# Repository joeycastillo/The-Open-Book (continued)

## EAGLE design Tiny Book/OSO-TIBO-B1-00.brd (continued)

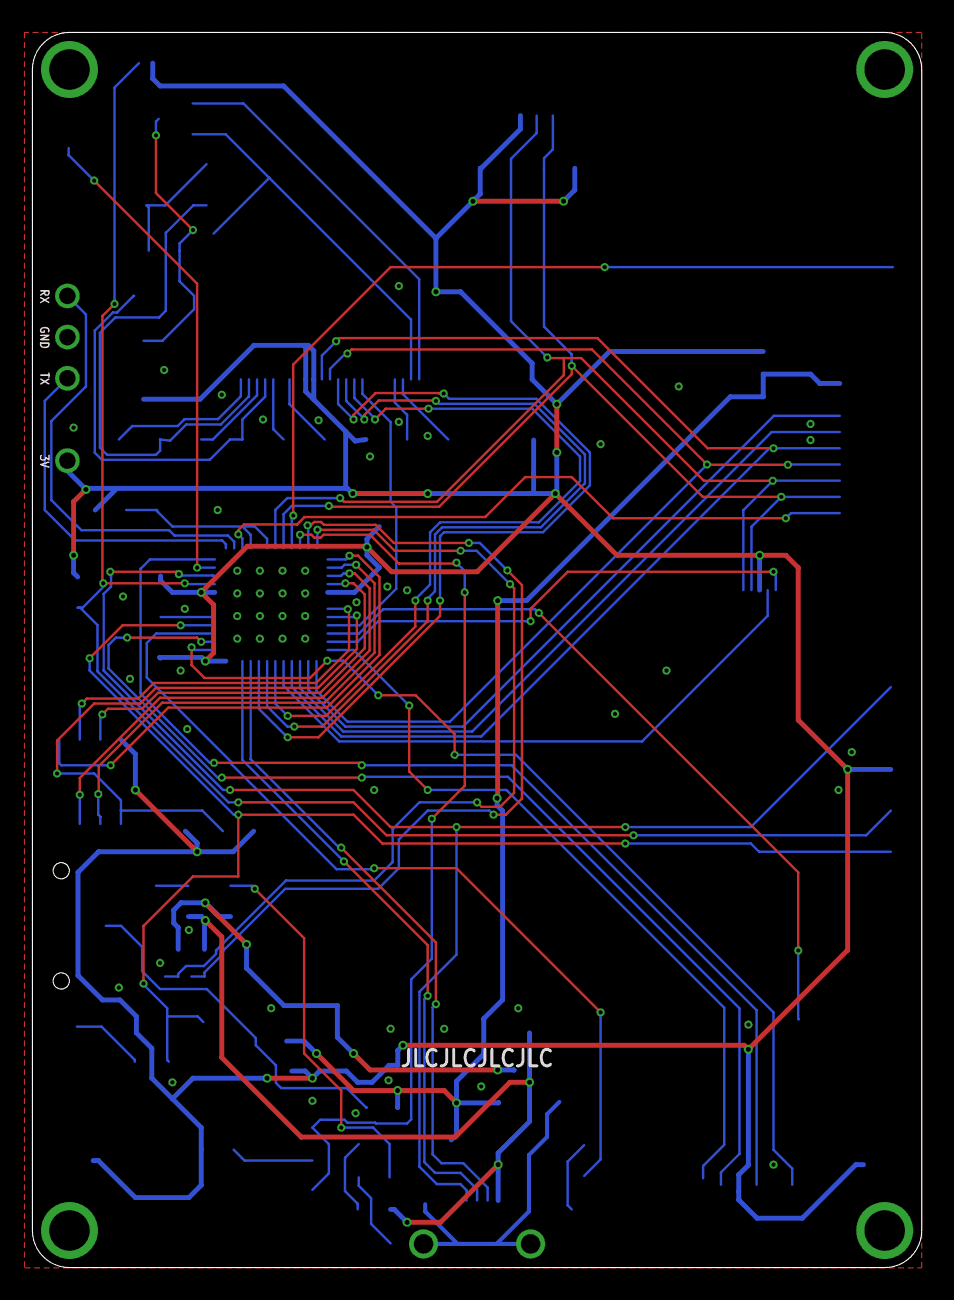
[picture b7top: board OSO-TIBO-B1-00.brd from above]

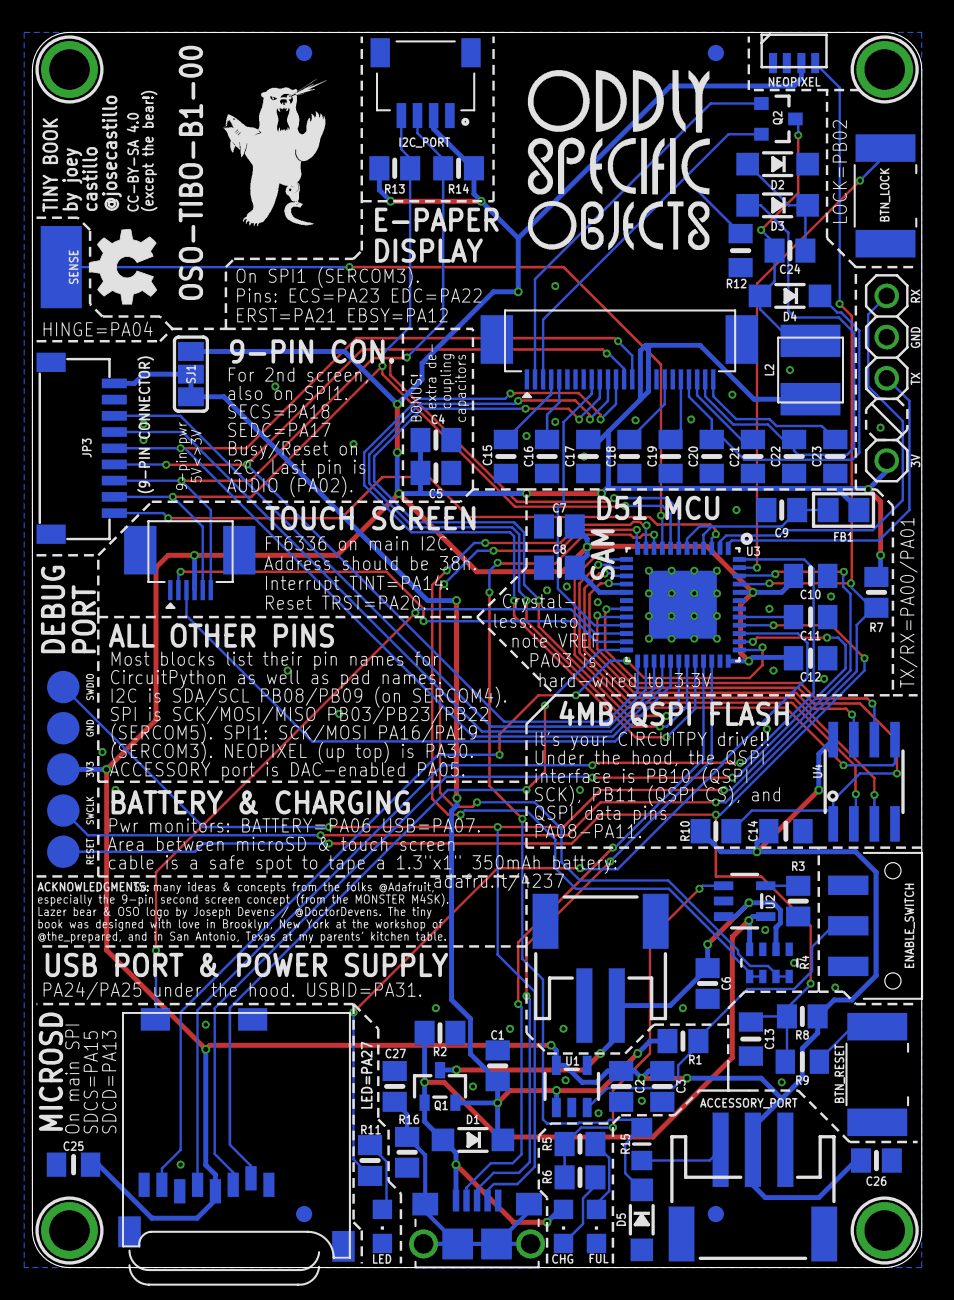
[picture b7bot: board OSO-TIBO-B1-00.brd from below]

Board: 2 copper layers, 54.9 x 76.2 mm, 90 parts (89 on the bottom side), 66 nets.

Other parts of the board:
U$37: OSO_WORDMARK_THREELINE_450MIL_1000DPI
U$44: OSO_BEAR_250X360MIL_1000DPI

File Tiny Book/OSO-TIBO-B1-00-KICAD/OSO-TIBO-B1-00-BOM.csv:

Reference, Quantity, Value, Footprint, Datasheet
ACCESSORY_PORT1 ,1,"JST PH 3","OSO-TIBO-B1-00:JSTPH3",""
BTN_LOCK1 BTN_RESET1 ,2,"SWITCH_PUSHBUTTONC&K_KSS","OSO-TIBO-B1-00:BTN_CK_KSS",""
C1 C2 C6 ,3,"10µF","OSO-TIBO-B1-00:0805-NO",""
C10 C11 C12 C14 C15 C16 C17 ,7,"1uF","OSO-TIBO-B1-00:0805_10MGAP",""
C13 ,1,"0.1uF","OSO-TIBO-B1-00:0805_10MGAP",""
C18 C19 C20 C21 C22 C23 ,6,"1uF/25V","OSO-TIBO-B1-00:0805_10MGAP",""
C24 ,1,"4.7uF/25V","OSO-TIBO-B1-00:0805-NO",""
C25 ,1,"10uF","OSO-TIBO-B1-00:0805_10MGAP",""
C27 ,1,"4.5nF","OSO-TIBO-B1-00:0805-NO",""
C3 C8 C9 ,3,"1uF","OSO-TIBO-B1-00:0805-NO",""
C5 ,1,"1µF","OSO-TIBO-B1-00:0805-NO",""
C26 C4 C7 ,3,"10uF","OSO-TIBO-B1-00:0805-NO",""
CHG1 ,1,"AMBER","OSO-TIBO-B1-00:CHIPLED_0805",""
D1 ,1,"MBR120","OSO-TIBO-B1-00:SOD-123",""
D2 D3 D4 ,3,"MBR0530","OSO-TIBO-B1-00:SOD-123",""
D5 ,1,"3.6V","OSO-TIBO-B1-00:SOD-123",""
ENABLE_SWITCH1 ,1,"JS102011SAQN","OSO-TIBO-B1-00:SW_JS102011SAQN",""
FB1 ,1,"Ferrite","OSO-TIBO-B1-00:0805",""
FID1 FID2 FID3 FID4 ,4,"FIDUCIAL_1MM","OSO-TIBO-B1-00:FIDUCIAL_1MM",""
FUL1 ,1,"GREEN","OSO-TIBO-B1-00:CHIPLED_0805",""
GOLD_ORB_SM1 ,1,"OSHWLOGOLOGO5MM","OSO-TIBO-B1-00:OSHW_5MM",""
I2C_PORT1 ,1,"SM04B-SRSS-TB(LF)(SN)","OSO-TIBO-B1-00:JST_SM04B-SRSS-TB(LF)(SN)",""
J2 ,1,"10118193-0001LF","OSO-TIBO-B1-00:FCI_10118193-0001LF",""
JP1 ,1,"PINHD-1X3","OSO-TIBO-B1-00:1X03",""
JP2 ,1,"PINHD-1X1","OSO-TIBO-B1-00:1X01",""
JP3 ,1,"HEADER-1X9_JSTSH","OSO-TIBO-B1-00:JST_SH9",""
L2 ,1,"10uH","OSO-TIBO-B1-00:MICROBUILDER_INDUCTOR_4X4MM_NR401_BIGPADS",""
LED1 ,1,"RED","OSO-TIBO-B1-00:CHIPLED_0805",""
MICROSD1 ,1,"MICROSD","OSO-TIBO-B1-00:MICROSD",""
NEOPIXEL1 ,1,"WS2812B_4020","OSO-TIBO-B1-00:WS2812B_4020",""
Q1 ,1,"DMG341","OSO-TIBO-B1-00:SOT23-R",""
Q2 ,1,"IRLML0100","OSO-TIBO-B1-00:SOT23-3",""
R1 R10 R13 R14 R3 R7 R8 ,7,"10K","OSO-TIBO-B1-00:0805-NO",""
R12 ,1,"0.47ohm","OSO-TIBO-B1-00:0805_10MGAP",""
R15 ,1,"1K","OSO-TIBO-B1-00:_0805MP",""
R16 ,1,"1M","OSO-TIBO-B1-00:0805-NO",""
R2 ,1,"100K","OSO-TIBO-B1-00:0805-NO",""
R4 ,1,"100K","OSO-TIBO-B1-00:EXBV8V",""
R11 R5 R6 ,3,"1K","OSO-TIBO-B1-00:0805-NO",""
R9 ,1,"100","OSO-TIBO-B1-00:0805_10MGAP",""
SENSE1 ,1,"SMD5","OSO-TIBO-B1-00:SMD2,54-5,08",""
SJ1 ,1,"SOLDERJUMPER_2WAY","OSO-TIBO-B1-00:SOLDERJUMPER_2WAY_OPEN_NOPASTE",""
TP1 TP2 TP3 TP4 TP5 ,5,"TESTPOINTROUND2MMNO","OSO-TIBO-B1-00:TESTPOINT_ROUND_2MM_NO",""
U$1 U$4 U$5 U$7 ,4,"MOUNTINGHOLE2.5","OSO-TIBO-B1-00:MOUNTINGHOLE_2.5_PLATED",""
U$31 ,1,"EINK_DISPLAY_TOUCH","OSO-TIBO-B1-00:EINK_DISPLAY_2_7_IN_TOUCH",""
U1 ,1,"AP2112-3.3","OSO-TIBO-B1-00:SOT23-5",""
U2 ,1,"MCP73831T-2ACI/OT","OSO-TIBO-B1-00:SOT23-5",""
U3 ,1,"ATSAMD51G18A-MUT","OSO-TIBO-B1-00:QFN48_7X7MC",""
U4 ,1,"GD25Q32C","OSO-TIBO-B1-00:MICROBUILDER_SOIC8_150MIL",""
X1 ,1,"JSTPH","OSO-TIBO-B1-00:JSTPH2",""

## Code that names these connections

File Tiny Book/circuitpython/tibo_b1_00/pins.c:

#include "shared-bindings/board/__init__.h"

#include "shared-module/displayio/__init__.h"

// This mapping only includes functional names because pins broken
// out on connectors are labeled with their MCU name available from
// microcontroller.pin.
STATIC const mp_rom_map_elem_t board_global_dict_table[] = {
    { MP_ROM_QSTR(MP_QSTR_AUDIO), MP_ROM_PTR(&pin_PA02) },

    { MP_ROM_QSTR(MP_QSTR_ACCESSORY), MP_ROM_PTR(&pin_PA05) },

    { MP_ROM_QSTR(MP_QSTR_SECS), MP_ROM_PTR(&pin_PA18) },
    { MP_ROM_QSTR(MP_QSTR_SEDC), MP_ROM_PTR(&pin_PA17) },

    { MP_ROM_QSTR(MP_QSTR_TINT), MP_ROM_PTR(&pin_PA14) },
    { MP_ROM_QSTR(MP_QSTR_TRST), MP_ROM_PTR(&pin_PA20) },

    { MP_ROM_QSTR(MP_QSTR_SCK), MP_ROM_PTR(&pin_PA17) },
    { MP_ROM_QSTR(MP_QSTR_MOSI), MP_ROM_PTR(&pin_PB23) },
    { MP_ROM_QSTR(MP_QSTR_MISO), MP_ROM_PTR(&pin_PB22) },

    { MP_ROM_QSTR(MP_QSTR_TX), MP_ROM_PTR(&pin_PA00) },
    { MP_ROM_QSTR(MP_QSTR_RX), MP_ROM_PTR(&pin_PA01) },

    { MP_ROM_QSTR(MP_QSTR_SDA), MP_ROM_PTR(&pin_PB08) },
    { MP_ROM_QSTR(MP_QSTR_SCL), MP_ROM_PTR(&pin_PB09) },

    { MP_ROM_QSTR(MP_QSTR_SDCS), MP_ROM_PTR(&pin_PA15) },
    { MP_ROM_QSTR(MP_QSTR_SDCD), MP_ROM_PTR(&pin_PA13) },

    { MP_ROM_QSTR(MP_QSTR_NEOPIXEL), MP_ROM_PTR(&pin_PA30) },

    { MP_ROM_QSTR(MP_QSTR_LED), MP_ROM_PTR(&pin_PA27) },

    { MP_ROM_QSTR(MP_QSTR_BATTERY), MP_ROM_PTR(&pin_PA06) },
    { MP_ROM_QSTR(MP_QSTR_USB), MP_ROM_PTR(&pin_PA07) },

    { MP_ROM_QSTR(MP_QSTR_I2C), MP_ROM_PTR(&board_i2c_obj) },
    { MP_ROM_QSTR(MP_QSTR_SPI), MP_ROM_PTR(&board_spi_obj) },
    { MP_ROM_QSTR(MP_QSTR_UART), MP_ROM_PTR(&board_uart_obj) },

    { MP_ROM_QSTR(MP_QSTR_DISPLAY), MP_ROM_PTR(&displays[0].display)}
};
MP_DEFINE_CONST_DICT(board_module_globals, board_global_dict_table);

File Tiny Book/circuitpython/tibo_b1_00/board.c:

/*
 * This file is part of the MicroPython project, http://micropython.org/
 *
 * The MIT License (MIT)
 *
 * Original copyright (c) 2017 Scott Shawcroft for Adafruit Industries
 *
 * Permission is hereby granted, free of charge, to any person obtaining a copy
 * of this software and associated documentation files (the "Software"), to deal
 * in the Software without restriction, including without limitation the rights
 * to use, copy, modify, merge, publish, distribute, sublicense, and/or sell
 * copies of the Software, and to permit persons to whom the Software is
 * furnished to do so, subject to the following conditions:
 *
 * The above copyright notice and this permission notice shall be included in
 * all copies or substantial portions of the Software.
 *
 * THE SOFTWARE IS PROVIDED "AS IS", WITHOUT WARRANTY OF ANY KIND, EXPRESS OR
 * IMPLIED, INCLUDING BUT NOT LIMITED TO THE WARRANTIES OF MERCHANTABILITY,
 * FITNESS FOR A PARTICULAR PURPOSE AND NONINFRINGEMENT. IN NO EVENT SHALL THE
 * AUTHORS OR COPYRIGHT HOLDERS BE LIABLE FOR ANY CLAIM, DAMAGES OR OTHER
 * LIABILITY, WHETHER IN AN ACTION OF CONTRACT, TORT OR OTHERWISE, ARISING FROM,
 * OUT OF OR IN CONNECTION WITH THE SOFTWARE OR THE USE OR OTHER DEALINGS IN
 * THE SOFTWARE.
 */

#include "boards/board.h"
#include "mpconfigboard.h"
#include "hal/include/hal_gpio.h"
#include "shared-bindings/board/__init__.h"
#include "shared-bindings/busio/SPI.h"
#include "shared-bindings/displayio/FourWire.h"
#include "shared-bindings/time/__init__.h"
#include "shared-module/displayio/__init__.h"
#include "shared-module/displayio/mipi_constants.h"

displayio_fourwire_obj_t board_display_obj;

#define DELAY 0x80
#define HEIGHT 264
#define WIDTH 176

uint8_t start_sequence[] = {
    0x00, 0x01, 0x9f, // panel setting: B&W only, custom LUT
    0x30, 0x01, 0x3a, // PLL
    0x01, 0x04, 0x03, 0x00, 0x2b, 0x2b, // power setting
    0x06, 0x03, 0x07, 0x07, 0x17, // booster soft start
    0x82, 0x01, 0x08, // VCOM
    0x50, 0x01, 0x07, // CDI
    0x61, 0x04, (WIDTH >> 8) & 0xFF, WIDTH & 0xFF, (HEIGHT >> 8) & 0xFF, HEIGHT & 0xFF, // Resolution
    0x16, 0x01, 0x00, // PDRF
    0x04, 0x00, // main screen turn on
};

uint8_t stop_sequence[] = {
    0x02, 0x01, 0x17  // Power off
};

void board_init(void) {
    busio_spi_obj_t* spi = &displays[0].fourwire_bus.inline_bus;
    common_hal_busio_spi_construct(spi, &pin_PA16, &pin_PA19, NULL);
    common_hal_busio_spi_never_reset(spi);

    displayio_fourwire_obj_t* bus = &displays[0].fourwire_bus;
    bus->base.type = &displayio_fourwire_type;
    common_hal_displayio_fourwire_construct(bus,
        spi,
        &pin_PA22, // EPD_DC Command or data
        &pin_PA23, // EPD_CS Chip select
        &pin_PA21, // EPD_RST Reset
        1000000, 0, 0);

    displayio_epaperdisplay_obj_t* display = &displays[0].epaper_display;
    display->base.type = &displayio_epaperdisplay_type;
    common_hal_displayio_epaperdisplay_construct(display,
        bus,
        start_sequence,
        sizeof(start_sequence),
        stop_sequence,
        sizeof(stop_sequence),
        WIDTH, // width
        HEIGHT, // height
        320, // RAM width
        300, // RAM height
        0, // colstart
        0, // rowstart
        0, // rotation
        NO_COMMAND, // set_column_window_command
        NO_COMMAND, // set_row_window_command
        NO_COMMAND, // set_current_column_command
        NO_COMMAND, // set_current_row_command
        0x13, // write_black_ram_command
        true, // black_bits_inverted
        NO_COMMAND, // write_color_ram_command (can add this for grayscale eventually)
        true, // color_bits_inverted
        0x000000, // highlight_color
        0x12, // refresh_display_command
        1, // refresh_time
        &pin_PA12, // busy_pin
        false, // busy_state
        0, // seconds_per_frame
        true); // chip_select (don't always toggle chip select)
}

bool board_requests_safe_mode(void) {
    return false;
}

void reset_board(void) {
}

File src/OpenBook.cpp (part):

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 @brief Configures the e-ink screen.
 @param srcs Chip select pin for the SRAM. Pass in OPENBOOK_NOT_PRESENT if you
             have omitted this chip.
 @param ecs Chip select pin for the e-ink screen.
 @param edc Data/command pin for the e-ink screen.
 @param erst Reset pin for the e-ink screen.
 @param ebsy Busy pin for the e-ink screen.
 @param spi Address of the SPI bus for the screen and SRAM chip.
 @param width Native width of the display
 @param height Native height of the display
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 @param clock Clock pin for the shift register
 @returns true as long as you passed in valid pins.
 @note This is currently the button solution for the Open Book. The Lock button
       is NOT on the shift register, though; it's on a SAMD51 interrupt pin, and
       SD Card Detect is on the shift register. This feels very inelegant and I
       may rework this in the final revision.
*/
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
/**
 @brief Configures the buttons for devices with a MCP23008 I2C port expander.
 @param interrupt The port expander's interrupt pin.
 @returns always returns true for now
 @note This is currently the button solution for the wing. All buttons are on
       the port expander, including the Lock button.
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    this->ioExpander = ioExpander;

    if (interrupt >= 0) {
        pinMode(interrupt, INPUT);
    }
    this->activeState = active;
    this->buttonInterrupt = interrupt;
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}

/**
 @brief Configures pins for audio input and output.
 @param left DAC pin for the left or mono channel.
 @param right DAC pin for the right channel, or OPENBOOK_NOT_PRESENT if using
              the wing where audio output is mono.
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                     breakout board into a STEMMA port, and get amplified mic
                     input that way; pass in A1 or A2, depending on the port you
                     are using.
 @returns true as long as at least one audio pin was configured.
*/
bool OpenBook::configureAudio(int8_t left, int8_t right, int8_t inlineMic, int8_t amplifiedMic) {
    int8_t channels = 0;
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
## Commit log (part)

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2019-08-14 remove 5V option, more complicated than I thought
2019-08-16 final commit of rev B as submitted to OSH Park
2019-08-16 add demo code from show and tell
2019-09-02 final tweaks and BOM for rev B
2019-09-03 added a rev C, embiggens the board at top
2019-09-09 eink display's tDocu layer was off, scooting it back into line with reality
2019-09-11 update readme with state of the project and goals
2019-09-13 lol nevermind this thru-hole switch is cheaper
2019-09-15 WIP samd51 ebook
2019-09-16 move traces out of text areas
2019-09-16 also tent power vias
2019-09-16 more documentation tweaks
2019-09-16 more label tweaks
2019-09-20 add logos and such
2019-09-23 wire FCS to M4's 'extra' pin
2019-09-24 move leds topside, thru-hole style. other design tweaks
2019-10-10 Digikey Bill of Materials
    Excludes e-ink panel from buyepaper.com
    Excludes microSD socket and SMT headers from Adafruit
    Includes Adafruit M4 Feather from Digikey
2019-10-10 Now includes MicroSD Socket from Digikey
    Excludes e-ink panel from buyepaper.com
    Excludes SMT headers from Adafruit
    Includes Adafruit M4 Feather from Digikey
    Includes MicroSD Socket from Digikey (instead of Adafruit)
2019-10-14 Make compatible with kitspace.org
2019-10-15 add these cool right-angle LEDs (that i ordered too many of)
2019-10-15 move surface mount chip away from thru-hole components
2019-10-16 last minute tweaks to text and arrangement
2019-10-17 yet more last minute text tweaks
2019-10-17 minor footprint and label tweaks
2019-10-17 final version of open book A1-01 submitted to OSH Park
2019-10-27 wip rev 2 with lessons learned
2019-10-29 rearrange power supply block, power neopixel from regulator
2019-10-29 fix buttons, add pulldown resistors & remove lock btn from shift reg
2019-10-29 silkscreen adjustments to ebook wing rev 3
2019-11-01 put sd card detect signal on shift register
2019-11-01 make the FCS jumper open by default
2019-11-04 route card detect signal
2019-11-04 improved silkscreen documentation
2019-11-04 scoot filter caps away from chip (easier for manual rework if needed)
2019-11-04 tweak documentation of QSPI flash
2019-11-05 more silkscreen tweaks
2019-11-05 renumber passives, update silkscreen
2019-11-05 improve clearance around C24
2019-11-05 draw outline around led
2019-11-05 correct component values
2019-11-05 remove wire stub
2019-11-06 add documentation to front side
2019-11-06 move SWCLK pullup to microcontroller block
2019-11-06 scoot swd connector up a bit
2019-11-07 fix typo
2019-11-07 more clearance around resistor arrays
2019-11-08 tweaks to front documentation
2019-11-08 restore reset stability circuit
2019-11-09 note LED pin on silkscreen
2019-11-09 tweak button labels
2019-11-09 make neopixel notes match other notes
2019-11-09 space out mic amp section for easier manual placement
2019-11-09 add OSHPark to colophon
2019-11-09 scoot OSO logo down
2019-11-09 final version of open book A1-02 submitted to OSH Park
2019-11-09 restore calvino quote, final version of wing A1-03 submitted to OSH Park
2019-11-10 add example sketch to test screen
2019-11-10 update readme with new photos
2019-11-12 add BOM to readme
2019-11-24 add mailing list signup link
2019-11-27 wip: open book arduino library
2019-11-28 update screen test to use open book arduino lib
2019-11-29 WIP custom driver for IL0398 e-ink controller
2019-11-30 invert busy logic to match panel spec
2019-11-30 typo on the silkscreen, correct pin numbers for button register
2019-11-30 clear shift register when setting up
2019-12-01 WIP open book rev 3?
2019-12-01 add indicator LED for full charge
2019-12-01 update quotes demo to use babel's word wrapping feature
2019-12-01 handle button active state as property, not macro
2019-12-02 partial update looks good
2019-12-03 set rotation in OpenBook, not display driver
2019-12-03 add board readme, mark rev 03 as WIP
2019-12-03 maybe power and gnd pads shouldn't be so close together
2019-12-06 starting over with next rev
2019-12-06 start rev 4, remove SRAM
2019-12-06 use max4468 for mic amp shutdown capability
2019-12-06 rev 3 (not made) just fixes a silkscreen typo
2019-12-06 rev 4: move babel chip into SRAM spot
2019-12-06 resistor array to monitor both VBAT and VBUS
2019-12-06 route A11/VBUSMON
2019-12-06 add green led for full battery
2019-12-06 fix typo in net name
2019-12-09 prettify voltage monitors in schematic
2019-12-10 readme tweak
2019-12-10 rename capacitors around samd51
2019-12-10 update 'building your board' silkscreen
2019-12-13 heart of darkness demo + voice commands
2019-12-26 more work on partial refresh
2019-12-27 new pin definitions for rev 4
2019-12-30 update README, main board image
2020-01-12 no need to resend waveforms; faster partial refresh
2020-01-14 this was a silly typo
2020-01-15 expose sd card as usb mass storage device
2020-01-20 let sketches decide how they want to use SD and flash
2020-01-20 add tiny book M4 board
2020-01-23 update README, board image
2020-01-25 better thru-hole button footprints, new right angle buttons
2020-01-25 connect shield to ground via RC (reduce headphone noise?)
2020-01-25 schematic cleanup
2020-01-25 right angle neopixel near reset button
2020-01-25 fix silksreen typo (serial is SERCOM5)
2020-01-25 DNP side buttons
2020-01-25 update README with rev 5 notes, add schematics
2020-01-25 WIP wing rev 5 with new buttons
2020-01-25 wing: new footprint for inductor
2020-01-25 fix new button labels
2020-01-25 rename alt buttons DNP
2020-01-25 wing: update to higher res OSO artwork
2020-01-28 if i do this again, accessory should be on PA05 to make use of the DAC
2020-01-28 swapped micraw and accessoory pins, need to route signals
2020-01-28 silkscreen and dimension tweaks
2020-01-28 surface mount reset button
2020-01-28 route accessory and mic raw signals
2020-01-28 use 4MB flash so babel can live there
2020-01-28 fix I2C routing snafu
2020-01-28 bump revision
2020-02-12 Add an OSH Park Link
    I had to dig on oshpark's sharing functionality to find the current rev of the board. It would be nice to link it from the README
2020-02-13 silkscreen updates to e-book wing
2020-02-13 rev 5 of the wing
2020-02-25 update BOM for wing rev 5
2020-03-03 [README] table headers copied at the end of table
    To help with readability since the table is quite long (avoid scrolling up / down to check which column is which)
2020-05-24 disable SRAM on feather M4
2020-05-24 MVBook update for e-book wing
2020-05-24 add sample books for MVBook
2020-06-05 last tweaks to A1-05 before sending to fab
2020-06-12 update BOM and gerbers for final rev of wing
2020-06-23 add method for getting sd card state
2020-06-23 fix audio channels
2020-06-23 add sketch to burn Open Book bootloader
2020-06-23 add pin definition for neopixel
2020-06-23 add open book system test sketch
2020-06-23 Buttons & SD card change
2020-06-24 rename example sketch
2020-06-25 last minute tweaks to system test
2020-06-27 document SD card detect method
2020-06-27 fix audio pin modes
2020-06-27 june README update, rev 5 board photos
2020-06-27 add hackaday.io link to readme
2020-07-04 remove old PCB design files
2020-07-07 update readme and BOM for kitspace
2020-07-07 update open book board notes
2020-07-07 include README.md in Kitspace pages
    We don't currently pick this up automatically for multi projects. You can point it at another readme if you have a board-specific one.
2020-07-07 add documentation printouts for both boards
2020-07-15 add C2 to e-book wing BOM
2020-07-16 fix R12 reference in the BOM
2020-07-20 e-book wing: fix one un-tented via
2020-08-13 tiny book!
2020-08-16 IL0398 driver: fix shades of gray
2020-08-17 add driver for IL91874 with grayscale mode
2020-08-21 no need to include these constants, already defined
2020-08-21 partial and quick modes for IL91874
2020-08-22 replace digireel part numbers with cut tape
2020-08-23 update BOM in documentation packet
2020-08-24 update wing setup guide
2020-08-28 add tiny book circuitpython board definition
2020-08-30 BOM links on kitspace were the wrong way round
    Link for featherwing took you to open book feather and vice versa. corrected, no other changes made.
2020-08-30 update materials for e-book wing A1-06
2020-08-30 use better microSD card slot
2020-09-13 book rev 6: pull-ups on SPI devices, headphone bias
2020-09-13 rotate OSO logo to match open book
2020-09-13 add gerbers for latest order
2020-10-01 move drill files to gerbers folder (#37)
2020-10-10 Open Book PCB Migration to KiCad
    This is a set of KiCad files from the posted Eagle files.
    For this conversion, the latest version Eagle files were used (OSO-BOOK-A1-06).
    The schematics were imported in three sheets, plus the cover sheet (total four).
    All text, net labels, global net labels, component values and references were adjusted to KiCad’s default size for consistency.
    Some nets were imported with net labels (because they were present only on one sheet) and some with global net labels (because they were used in multiple sheets).
    All duplicate global net labels were deleted from power nets (power nets are global nets by default).
2020-10-10 BTN_LOCK1 silkscreen location adjustment
2020-10-11 E-Book Feather Wing PCB Migration to KiCad
    This is a set of KiCad files from the posted Eagle files.
    For this conversion, the latest version Eagle files were used (OSO-BOWI-A1-06).
    The schematic was imported in a single sheet.
    All text, net labels, global net labels, component values and references were adjusted to KiCad’s default size for consistency.
    All duplicate global net labels were deleted from power nets (power nets are global nets by default).
    The converted libraries (symbol and footprints) were examined for accuracy.
2020-10-11 Tiny Book (OSO-TIBO-B2-00) Migration to KiCad
2020-10-13 add circuitpython EPD drivers
2020-10-14 Revised E-Book Wing silkscreen labels.
    Addressing comment for the solder jumpers on the E-Book Wing that had silkscreen labels, such as TX1/RX1/ECS1 etc, where the number 1 was appended after the original name, which was crowding the labe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
2020-10-19 add link to e-book wing assembly video
2020-10-29 fix mic preamp glitch in system test
2020-10-30 experiment for use with textformat branch of babel
2020-10-30 add documentation for BOOK A1 rev 06
2020-10-30 point kitspace to revision 06 of book
2020-10-30 add 3D models of book and wing
2020-10-30 update readme and schematics
2020-10-30 add acknowledgements for 3d models
2020-10-30 fix small typo in readme
2020-10-30 add render images / rename for consistency
2020-11-01 1-click BOM: fix typo
2020-11-01 MVBook: support multi-page menu
2020-11-01 store user's place in book
2020-11-01 update roadmap in README
2020-11-03 MVBook: add screen lock, splash screen at boot
2020-11-03 MVBook: improve menu system responsiveness
2020-12-01 first crack at ESP32-S2 Open Book
2020-12-04 Update open-book-printout.md
    Fix broken(?) link to Arduino library manager URL
2020-12-12 examples: add shebang to bookbinder.py (fixes #45)
2020-12-16 fix incorrect part number in e-book wing BOM
2020-12-22 Alternative parts for ESP32-S2 version
    - changed USB-C connector (https://lcsc.com/product-detail/USB-Type-C_Korean-Hroparts-Elec-TYPE-C-31-M-12_C165948.html)
    - changed uSD card slot (https://www.aliexpress.com/item/32763208642.html)
    - added cutout for ESP32-S2 PCB antena
2020-12-22 Revert "Buttons & SD card change"
    This reverts commit 564ec3b5048e0d7899cd32f6cb14d9a07736022d.
2021-06-06 open book abridged with castellated EPD driver
2022-07-22 Fix word order typo.
    s/some stopped/stopped some/
2022-09-28 project reboot
2022-09-28 add pi pico book, new castellated module
2022-09-28 add note on where to find firmware
2022-09-28 fix link
2022-09-28 typo
2022-11-09 add 3d printed case design
2022-11-15 rev 5: remove zener diodes, silkscreen tweaks
2022-11-15 shrink outline of JLC module, size minimum no longer applies
2022-11-15 add kistpace files
2022-11-19 docs: Adds License to readme
    Would resolve https://github.com/joeycastillo/The-Open-Book/issues/63 if merged
2022-11-29 update JLC fabrication files
2022-12-07 Update documentation links (fixes #66)
2022-12-16 Fix capacitor part number
2023-07-03 convert castellated e-paper driver project to KiCAD
2023-07-21 ESP32-S3 book, rev 0 fabricated july 2023
2023-08-30 rev 06
2023-08-30 add EN pullup to ESP32-S3 book
